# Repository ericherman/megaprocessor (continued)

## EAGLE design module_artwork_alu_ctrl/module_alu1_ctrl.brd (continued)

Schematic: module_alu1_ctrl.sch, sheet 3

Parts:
CMP88, CMP92, CMP94: BUS_SPLIT_DISPLAY

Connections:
BUS_DECODE_ALU_1: CMP92.INPUT
BUS_DECODE_ALU_2: CMP88.INPUT
BUS_DECODE_ALU_3: CMP94.INPUT
K_0: CMP94.P$7 (OUT_6); also elsewhere on the board
K_1: CMP94.P$8 (OUT_7); also elsewhere on the board
K_N: CMP94.P$9 (OUT_8); also elsewhere on the board
OPCODE_IS_ABS: CMP88.P$14 (OUT_13); also elsewhere on the board
OPCODE_IS_ADDQ_GROUP: CMP94.P$6 (OUT_5); also elsewhere on the board
OPCODE_IS_ADDX: CMP88.P$12 (OUT_11); also elsewhere on the board
OPCODE_IS_ADD_GROUP: CMP88.P$9 (OUT_8); also elsewhere on the board
OPCODE_IS_ADD_SP_STATE_2: CMP92.P$15 (OUT_14); also elsewhere on the board
OPCODE_IS_AND_GROUP: CMP88.P$8 (OUT_7); also elsewhere on the board
OPCODE_IS_BIT_XX: CMP88.P$5 (OUT_4); also elsewhere on the board
OPCODE_IS_BIT_XX_N: CMP94.P$2 (OUT_1); also elsewhere on the board
OPCODE_IS_BXX_STATE_2: CMP88.P$1 (OUT_0); also elsewhere on the board
OPCODE_IS_CMP: CMP94.P$1 (OUT_0); also elsewhere on the board
OPCODE_IS_CMP_GROUP: CMP94.P$10 (OUT_9); also elsewhere on the board
OPCODE_IS_DIV: CMP88.P$15 (OUT_14); also elsewhere on the board
OPCODE_IS_DIVS_STATE_0: CMP92.P$2 (OUT_1); also elsewhere on the board
OPCODE_IS_DIV_STATE_0: CMP92.P$7 (OUT_6); also elsewhere on the board
OPCODE_IS_INDIRECT_POSTINC: CMP92.P$9 (OUT_8); also elsewhere on the board
OPCODE_IS_INV: CMP94.P$3 (OUT_2); also elsewhere on the board
OPCODE_IS_JMP_R0: CMP92.P$11 (OUT_10); also elsewhere on the board
OPCODE_IS_JSR_ABS: CMP92.P$14 (OUT_13); also elsewhere on the board
OPCODE_IS_JSR_R0: CMP92.P$5 (OUT_4); also elsewhere on the board
OPCODE_IS_JSR_X_STATE_7: CMP92.P$8 (OUT_7); also elsewhere on the board
OPCODE_IS_LOGIC_GROUP: CMP88.P$3 (OUT_2); also elsewhere on the board
OPCODE_IS_MOVER: CMP94.P$11 (OUT_10); also elsewhere on the board
OPCODE_IS_MOVE_R0_SP_STATE_0: CMP92.P$12 (OUT_11); also elsewhere on the board
OPCODE_IS_MOVE_SP_R0: CMP92.P$10 (OUT_9); also elsewhere on the board
OPCODE_IS_MULS: CMP88.P$13 (OUT_12); also elsewhere on the board
OPCODE_IS_MUL_N: CMP92.P$13 (OUT_12); also elsewhere on the board
OPCODE_IS_NEG: CMP88.P$4 (OUT_3); also elsewhere on the board
OPCODE_IS_NEGX: CMP88.P$10 (OUT_9); also elsewhere on the board
OPCODE_IS_OR: CMP88.P$7 (OUT_6); also elsewhere on the board
OPCODE_IS_OR_GROUP: CMP94.P$12 (OUT_11); also elsewhere on the board
OPCODE_IS_PUSH_PS: CMP92.P$3 (OUT_2); also elsewhere on the board
OPCODE_IS_PUSH_RA: CMP92.P$4 (OUT_3); also elsewhere on the board
OPCODE_IS_SHIFT_XX: CMP88.P$2 (OUT_1); also elsewhere on the board
OPCODE_IS_SQRT: CMP88.P$16 (OUT_15); also elsewhere on the board
OPCODE_IS_STACK_GROUP: CMP94.P$5 (OUT_4); also elsewhere on the board
OPCODE_IS_STACK_REL_STATE_2: CMP92.P$16 (OUT_15); also elsewhere on the board
OPCODE_IS_SUB: CMP88.P$6 (OUT_5); also elsewhere on the board
OPCODE_IS_SUBX: CMP88.P$11 (OUT_10); also elsewhere on the board
OPCODE_IS_SUB_GROUP: CMP94.P$4 (OUT_3); also elsewhere on the board
OPCODE_IS_TRAP: CMP92.P$6 (OUT_5); also elsewhere on the board
OPCODE_IS_XOR_GROUP: CMP94.P$13 (OUT_12); also elsewhere on the board
SHIFT_IS_SHIFTING: CMP92.P$1 (OUT_0); also elsewhere on the board

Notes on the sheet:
clBit shift_is_shifting; // 0 clBit opcode_is_divs_state_0; // 1 clBit opcode_is_push_ps; // 2 clBit opcode_is_push_ra; // 3 clBit opcode_is_jsr_r0; // 4 clBit opcode_is_trap; // 5 clBit opcode_is_div_state_0; // 6 clBit opcode_is_jsr_x_state_7; // 7 clBit opcode_is_indirect_postinc; // 8 clBit opc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
clBit opcode_is_bxx_state_2; // 0 clBit opcode_is_shift_xx; // 1 clBit opcode_is_logic_group; // 2 clBit opcode_is_neg; // 3 clBit opcode_is_bit_xx; // 4 clBit opcode_is_sub; // 5 clBit opcode_is_or; // 6 clBit opcode_is_and_group; // 7 clBit opcode_is_add_group; // 8 clBit opcode_is_negx; // 9 clB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
clBit opcode_is_cmp; // 0 clBit opcode_is_bit_xx_n; // 1 clBit opcode_is_inv; // 2 clBit opcode_is_sub_group; // 3 clBit opcode_is_stack_group; // 4 clBit opcode_is_addq_group; // 5 clBit k_0; // 6 clBit k_1; // 7 clBit k_m; // 8 clBit opcode_is_cmp_group; // 9 clBit opcode_is_mover; // 10 clBit op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

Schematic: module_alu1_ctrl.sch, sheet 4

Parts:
CMP35: DECODER16
CMP39: BUS_CONSTRUCT_DISPLAY; BUS_SPLIT_DISPLAY
CMP40: BUS_2_BUS; BUS2BUS

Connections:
H_1: CMP35.A1; also elsewhere on the board
H_2: CMP35.A2; also elsewhere on the board
H_3: CMP35.A3; also elsewhere on the board
unnamed: CMP35.P0, CMP39.P$15 (IN_14)
unnamed: CMP35.P1, CMP39.P$14 (IN_13)
unnamed: CMP35.P2, CMP39.P$13 (IN_12)
unnamed: CMP35.P3, CMP39.P$12 (IN_11)
unnamed: CMP35.P4, CMP39.P$11 (IN_10)
unnamed: CMP35.P5, CMP39.P$10 (IN_9)
unnamed: CMP35.P6, CMP39.P$9 (IN_8)
unnamed: CMP35.P7, CMP39.P$8 (IN_7)
unnamed: CMP35.P8, CMP39.P$7 (IN_6)
unnamed: CMP35.P9, CMP39.P$6 (IN_5)
unnamed: CMP35.P10, CMP39.P$5 (IN_4)
unnamed: CMP35.P11, CMP39.P$4 (IN_3)
unnamed: CMP35.P12, CMP39.P$3 (IN_2)
unnamed: CMP35.P13, CMP39.P$2 (IN_1)
unnamed: CMP35.P14, CMP39.P$1 (IN_0)
unnamed: CMP35.P15, CMP39.P$16 (IN_15)
unnamed: CMP39.INPUT (OUT), CMP40.P$1 (IN)

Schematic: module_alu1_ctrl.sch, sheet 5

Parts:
CMP10: DECODER4
CMP20: 2AND
CMP24, CMP27: 2OR
CMP26: 8OR
CMP41: 1BUF

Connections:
ALU1_X_MUX_RA__SET_A: CMP26.OUT_P; also elsewhere on the board
ALU1_X_MUX_SHIFT_R3: CMP27.OUT_P; also elsewhere on the board
ALU1_X_MUX_SHIFT_R3_N: CMP27.OUT_M (N); also elsewhere on the board
BIT_SELECT_ENABLE: CMP41.N; also elsewhere on the board
BIT_SHIFT_MODE_CHANGE__ARITH: CMP10.P1; also elsewhere on the board
BIT_SHIFT_MODE_CLEAR__ROTATE: CMP10.P2; also elsewhere on the board
BIT_SHIFT_MODE_CLEAR__ROTATE_N: CMP10.N2; also elsewhere on the board
BIT_SHIFT_MODE_SET__X_ROT: CMP10.P3; also elsewhere on the board
BIT_SHIFT_MODE_TEST__LOGICAL: CMP10.P0
BIT_XX_ACTION_CYCLE: CMP24.OUT_M (N), CMP26.3 (2); also elsewhere on the board
BIT_XX_LOAD_CYCLE: CMP20.OUT_P; also elsewhere on the board
H_6: CMP10.A0; also elsewhere on the board
H_7: CMP10.A1; also elsewhere on the board
OPCODE_IS_ADDQ_GROUP: CMP26.6 (5); also elsewhere on the board
OPCODE_IS_ADD_GROUP: CMP26.2 (1); also elsewhere on the board
OPCODE_IS_AND_GROUP: CMP26.1 (0); also elsewhere on the board
OPCODE_IS_BIT_XX: CMP20.P$1 (1); also elsewhere on the board
OPCODE_IS_BIT_XX_N: CMP24.P$2 (A1); also elsewhere on the board
OPCODE_IS_CMP: CMP26.5 (4); also elsewhere on the board
OPCODE_IS_INV: CMP41.IN; also elsewhere on the board
OPCODE_IS_OR_GROUP: CMP26.8 (7); also elsewhere on the board
OPCODE_IS_SUB: CMP26.7 (6); also elsewhere on the board
OPCODE_IS_XOR_GROUP: CMP26.4 (3); also elsewhere on the board
STATE_1: CMP20.P$2 (2), CMP24.P$1 (A2); also elsewhere on the board
STATE_11: CMP27.P$1 (A2); also elsewhere on the board
STATE_13: CMP27.P$2 (A1); also elsewhere on the board

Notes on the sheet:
bit_select_enable = ~bus_decode_alu_1.opcode_is_inv;
bit_xx_load_cycle = Cpnt_2AND(bus_decode_alu_2.opcode_is_bit_xx, bus_state[1]);
bit_xx_action_cycle = ~Cpnt_2OR(bus_decode_alu_3.opcode_is_bit_xx_n, bus_state[1]);
alu1_x_mux_RA__set_A = Cpnt_8OR(bus_decode_alu_1.opcode_is_add_group, bus_decode_alu_1.opcode_is_addq_group, bus_decode_alu_1.opcode_is_sub, bus_decode_alu_1.opcode_is_cmp, bus_decode_alu_1.opcode_is_and_group, bus_decode_alu_1.opcode_is_or_group, bus_decode_alu_1.opcode_is_xor_group, bit_xx_action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
alu1_x_mux_shift_r3 = Cpnt_2OR(bus_state[13], bus_state[11]);

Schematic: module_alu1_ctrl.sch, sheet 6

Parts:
CMP28, CMP33: 2X2AND_OR
CMP29: 8OR
CMP30: 3OR
CMP31: 4OR
CMP32: 2AND

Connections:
ADDER_X_SPECIAL: CMP28.P$2 (A1); also elsewhere on the board
ADDER_Y_SPECIAL: CMP29.2 (1); also elsewhere on the board
ALU1_X_MUX_RA: CMP28.OUT_P; also elsewhere on the board
ALU1_X_MUX_RA__SET_A: CMP28.P$4 (B1); also elsewhere on the board
ALU1_X_MUX_SHIFT_R3_N: CMP28.P$1 (A0), CMP28.P$3 (B0); also elsewhere on the board
ALU1_Y_MUX_BIT: CMP32.OUT_P; also elsewhere on the board
ALU1_Y_MUX_K: CMP31.OUT_P; also elsewhere on the board
ALU1_Y_MUX_NOT_BIT: CMP33.OUT_P; also elsewhere on the board
ALU1_Y_MUX_RB: CMP30.OUT_P; also elsewhere on the board
ALU1_Y_MUX_RB_A: CMP29.OUT_P, CMP30.P$3 (2)
BIT_SHIFT_MODE_CLEAR__ROTATE: CMP33.P$3 (B0); also elsewhere on the board
BIT_SHIFT_MODE_CLEAR__ROTATE_N: CMP32.P$1 (1); also elsewhere on the board
BIT_XX_ACTION_CYCLE: CMP32.P$2 (2), CMP33.P$4 (B1); also elsewhere on the board
BIT_XX_LOAD_CYCLE: CMP30.P$1 (0); also elsewhere on the board
FLAG_F3: CMP31.1 (0); also elsewhere on the board
OPCODE_IS_ADDQ_GROUP: CMP31.2 (1); also elsewhere on the board
OPCODE_IS_ADD_GROUP: CMP29.4 (3); also elsewhere on the board
OPCODE_IS_AND_GROUP: CMP29.8 (7); also elsewhere on the board
OPCODE_IS_CMP_GROUP: CMP29.3 (2); also elsewhere on the board
OPCODE_IS_INV: CMP33.P$1 (A0), CMP33.P$2 (A1); also elsewhere on the board
OPCODE_IS_MOVER: CMP29.5 (4); also elsewhere on the board
OPCODE_IS_OR: CMP29.7 (6); also elsewhere on the board
OPCODE_IS_SHIFT_XX: CMP30.P$2 (1); also elsewhere on the board
OPCODE_IS_STACK_GROUP: CMP31.3 (2); also elsewhere on the board
OPCODE_IS_SUB_GROUP: CMP29.1 (0); also elsewhere on the board
OPCODE_IS_XOR_GROUP: CMP29.6 (5); also elsewhere on the board
STATE_13: CMP31.4 (3); also elsewhere on the board

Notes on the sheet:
alu1_x_mux_RA = Cpnt_2x2AND_OR(alu1_x_mux_RA__set_A, ~alu1_x_mux_shift_r3, bus_rnx_specials.adder_x_special,~alu1_x_mux_shift_r3);
alu1_y_mux_RB_A = Cpnt_8OR(bus_decode_alu_1.opcode_is_and_group, bus_decode_alu_1.opcode_is_or, bus_decode_alu_1.opcode_is_xor_group, bus_decode_alu_1.opcode_is_mover, bus_decode_alu_1.opcode_is_add_group, bus_decode_alu_1.opcode_is_sub_group, bus_decode_alu_1.opcode_is_cmp_group, bus_rnx_specials.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
alu1_y_mux_RB = Cpnt_3OR(alu1_y_mux_RB_A, bus_decode_alu_2.opcode_is_shift_xx, bit_xx_load_cycle);
alu1_y_mux_k = Cpnt_4OR(bus_decode_alu_1.opcode_is_addq_group, bus_decode_alu_1.opcode_is_stack_group, bus_state[13], bus_PS[WiC_PS_FLAG_INDEX_F3]);
alu1_y_mux_bit = Cpnt_2AND(bit_xx_action_cycle, ~bit_shift_mode_decode.Output()[BIT_SHIFT_MODE_CLEAR]);
alu1_y_mux_not_bit = Cpnt_2x2AND_OR(bit_xx_action_cycle, bit_shift_mode_decode.Output()[BIT_SHIFT_MODE_CLEAR], bus_decode_alu_1.opcode_is_inv, bus_decode_alu_1.opcode_is_inv);

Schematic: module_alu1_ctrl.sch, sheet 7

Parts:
CMP3: 2AND
CMP4: 2X2AND_OR
CMP5: 8OR
CMP6: 2OR
CMP7: 4X2AND_OR
CMP57: 1BUF

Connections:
ADD1_CARRY_INPUT_BIT: CMP7.OUT_P; also elsewhere on the board
ADD1_DO_SUBTRACT: CMP5.OUT_P, CMP7.P$3 (B0); also elsewhere on the board
DO_SUBTRACT__SET_A: CMP4.OUT_P, CMP5.7 (6)
FLAG_X: CMP7.P$7 (D0), CMP57.IN; also elsewhere on the board
FLAG_X_N: CMP7.P$5 (C0), CMP57.N
H_4: CMP3.P$1 (1); also elsewhere on the board
unnamed: CMP7.P$1 (A0), CMP7.P$2 (A1)
NEGATE_FOR_SHIFT: CMP3.OUT_P, CMP5.2 (1)
OPCODE_IS_ABS: CMP4.P$4 (B1); also elsewhere on the board
OPCODE_IS_ADDX: CMP7.P$8 (D1); also elsewhere on the board
OPCODE_IS_CMP: CMP5.3 (2); also elsewhere on the board
OPCODE_IS_DIV: CMP5.8 (7); also elsewhere on the board
OPCODE_IS_MULS: CMP4.P$2 (A1); also elsewhere on the board
OPCODE_IS_NEGX: CMP5.5 (4), CMP6.P$1 (A2); also elsewhere on the board
OPCODE_IS_SHIFT_XX: CMP3.P$2 (2); also elsewhere on the board
OPCODE_IS_SQRT: CMP5.1 (0); also elsewhere on the board
OPCODE_IS_SUBX: CMP5.4 (3), CMP6.P$2 (A1); also elsewhere on the board
OPCODE_IS_SUBX_NEGX: CMP6.OUT_P, CMP7.P$6 (C1)
OPCODE_IS_SUBX_NEGX_N: CMP6.OUT_M (N), CMP7.P$4 (B1)
OPCODE_IS_SUB_GROUP: CMP5.6 (5); also elsewhere on the board
RA_MUX_IS_N: CMP4.P$3 (B0); also elsewhere on the board
STATE_3: CMP4.P$1 (A0); also elsewhere on the board

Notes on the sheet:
negate_for_shift = Cpnt_2AND(bus_decode_alu_2.opcode_is_shift_xx, bus_H[4]);
add1_do_subtract__set_A = Cpnt_2x2AND_OR(bus_decode_alu_2.opcode_is_abs, bus_ra_flags.RA_mux_is_n, bus_decode_alu_2.opcode_is_muls, bus_state[3]);
add1_do_subtract = Cpnt_8OR(bus_decode_alu_1.opcode_is_sub_group, bus_decode_alu_1.opcode_is_cmp, bus_decode_alu_2.opcode_is_subx, bus_decode_alu_2.opcode_is_negx, add1_do_subtract__set_A, bus_decode_alu_2.opcode_is_sqrt, bus_decode_alu_2.opcode_is_div, negate_for_shift); // MOPUP
opcode_is_subx_negx = Cpnt_2OR(bus_decode_alu_2.opcode_is_subx, bus_decode_alu_2.opcode_is_negx);
add1_input_carry_bit = Cpnt_4x2AND_OR(bus_decode_alu_2.opcode_is_addx, bus_PS[WiC_PS_FLAG_INDEX_X], // ADDX opcode_is_subx_negx, ~bus_PS[WiC_PS_FLAG_INDEX_X], // SUBX ~opcode_is_subx_negx, add1_do_subtract, // SUB BIT_VAL_0,BIT_VAL_0); // MOPUP

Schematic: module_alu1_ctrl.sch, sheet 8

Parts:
CMP2, CMP8: 3OR
CMP9: 2OR
CMP25, CMP38: 1BUF
CMP36, CMP37: 3AND

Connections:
H_4: CMP38.IN; also elsewhere on the board
IS_SHIFTING_LEFT: CMP36.OUT_P; also elsewhere on the board
IS_SHIFTING_RIGHT: CMP37.OUT_P; also elsewhere on the board
OPCODE_IS_ADDQ_GROUP: CMP2.P$2 (1); also elsewhere on the board
OPCODE_IS_ADDX: CMP2.P$3 (2); also elsewhere on the board
OPCODE_IS_ADD_GROUP: CMP2.P$1 (0); also elsewhere on the board
OPCODE_IS_CMP: CMP8.P$3 (2); also elsewhere on the board
OPCODE_IS_NEG: CMP9.P$1 (A2); also elsewhere on the board
OPCODE_IS_NEGX: CMP9.P$2 (A1); also elsewhere on the board
OPCODE_IS_SHIFT_XX: CMP36.P$3 (3), CMP37.P$3 (3); also elsewhere on the board
OPCODE_IS_SUB: CMP8.P$1 (0); also elsewhere on the board
OPCODE_IS_SUBX: CMP8.P$2 (1); also elsewhere on the board
SHIFT_LEFT: CMP36.P$1 (1), CMP38.N
SHIFT_RIGHT: CMP37.P$2 (2), CMP38.P
STATE_1: CMP25.IN; also elsewhere on the board
STATE_1_N: CMP25.N, CMP36.P$2 (2), CMP37.P$1 (1); also elsewhere on the board
USE_ADD_V: CMP2.OUT_P; also elsewhere on the board
USE_NEG_V: CMP9.OUT_P; also elsewhere on the board
USE_SUB_V: CMP8.OUT_P; also elsewhere on the board

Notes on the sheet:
use_add_V = Cpnt_3OR(bus_decode_alu_1.opcode_is_add_group, bus_decode_alu_1.opcode_is_addq_group, bus_decode_alu_2.opcode_is_addx);
use_sub_V = Cpnt_3OR(bus_decode_alu_1.opcode_is_sub, bus_decode_alu_1.opcode_is_cmp, bus_decode_alu_2.opcode_is_subx);
use_neg_V = Cpnt_2OR(bus_decode_alu_2.opcode_is_neg,bus_decode_alu_2.opcode_is_negx);
is_shifting_right = Cpnt_3AND(bus_decode_alu_2.opcode_is_shift_xx, bus_H[4], ~bus_state[1]);
is_shifting_left = Cpnt_3AND(bus_decode_alu_2.opcode_is_shift_xx, ~bus_H[4], ~bus_state[1]);

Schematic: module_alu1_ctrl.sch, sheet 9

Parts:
CMP11, CMP16, CMP19, CMP23: 2AND
CMP18: 2OR
CMP34: 3OR

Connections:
ARITH_RIGHT_INPUT: CMP19.OUT_P, CMP34.P$1 (0)
BIT_SHIFT_MODE_CHANGE__ARITH: CMP19.P$1 (1); also elsewhere on the board
BIT_SHIFT_MODE_CLEAR__ROTATE: CMP16.P$1 (1), CMP23.P$1 (1); also elsewhere on the board
BIT_SHIFT_MODE_SET__X_ROT: CMP11.P$1 (1); also elsewhere on the board
FLAG_X: CMP11.P$2 (2); also elsewhere on the board
LEFT_SHIFT_INPUT: CMP18.OUT_P; also elsewhere on the board
RA_MUX_IS_N: CMP16.P$2 (2), CMP19.P$2 (2); also elsewhere on the board
RA_MUX_LSB: CMP23.P$2 (2); also elsewhere on the board
RIGHT_SHIFT_INPUT: CMP34.OUT_P; also elsewhere on the board
ROT_LEFT_INPUT: CMP16.OUT_P, CMP18.P$2 (A1)
ROT_RIGHT_INPUT: CMP23.OUT_P, CMP34.P$3 (2)
X_ROT_INPUT: CMP11.OUT_P, CMP18.P$1 (A2), CMP34.P$2 (1)

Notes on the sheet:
x_rot_input = Cpnt_2AND(bit_shift_mode_decode.Output()[BIT_SHIFT_MODE_X_ROT], bus_PS[WiC_PS_FLAG_INDEX_X]);
rot_left_input = Cpnt_2AND(bit_shift_mode_decode.Output()[BIT_SHIFT_MODE_ROTATE], bus_ra_flags.RA_mux_is_n);
left_shift_input = Cpnt_2OR(rot_left_input, x_rot_input);
arith_right_input = Cpnt_2AND(bit_shift_mode_decode.Output()[BIT_SHIFT_MODE_ARITH], bus_ra_flags.RA_mux_is_n);
rot_right_input = Cpnt_2AND(bit_shift_mode_decode.Output()[BIT_SHIFT_MODE_ROTATE], bus_ra_flags.RA_mux_lsb);
right_shift_input = Cpnt_3OR(arith_right_input, rot_right_input, x_rot_input);

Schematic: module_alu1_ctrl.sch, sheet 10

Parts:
CMP42, CMP43, CMP45: 2X2AND_OR
CMP44: 2OR
CMP46: 3OR

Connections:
ALU1_OUTPUT_MUX_ADDER: CMP46.OUT_M (N); also elsewhere on the board
ALU1_OUTPUT_MUX_LOGIC: CMP45.OUT_P, CMP46.P$3 (2); also elsewhere on the board
AND: CMP42.OUT_P, CMP44.P$2 (A1); also elsewhere on the board
BIT_SHIFT_MODE_CLEAR__ROTATE: CMP42.P$3 (B0); also elsewhere on the board
BIT_SHIFT_MODE_SET__X_ROT: CMP43.P$3 (B0); also elsewhere on the board
IS_SHIFTING_LEFT: CMP46.P$2 (1); also elsewhere on the board
IS_SHIFTING_RIGHT: CMP46.P$1 (0); also elsewhere on the board
OPCODE_IS_AND_GROUP: CMP42.P$1 (A0), CMP42.P$2 (A1); also elsewhere on the board
OPCODE_IS_BIT_XX: CMP42.P$4 (B1), CMP43.P$4 (B1), CMP45.P$4 (B1); also elsewhere on the board
OPCODE_IS_LOGIC_GROUP: CMP45.P$1 (A0), CMP45.P$2 (A1); also elsewhere on the board
OPCODE_IS_OR: CMP43.P$1 (A0), CMP43.P$2 (A1); also elsewhere on the board
OR: CMP43.OUT_P, CMP44.P$1 (A2); also elsewhere on the board
STATE_1_N: CMP45.P$3 (B0); also elsewhere on the board
XOR: CMP44.OUT_M (N); also elsewhere on the board

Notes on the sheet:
logic_output_mux_and = Cpnt_2x2AND_OR(bus_decode_alu_2.opcode_is_bit_xx, bit_shift_mode_decode.Output()[BIT_SHIFT_MODE_CLEAR], bus_decode_alu_1.opcode_is_and_group, bus_decode_alu_1.opcode_is_and_group);
logic_output_mux_or = Cpnt_2x2AND_OR(bus_decode_alu_2.opcode_is_bit_xx, bit_shift_mode_decode.Output()[BIT_SHIFT_MODE_SET], bus_decode_alu_1.opcode_is_or, bus_decode_alu_1.opcode_is_or);
logic_output_mux_xor = ~Cpnt_2OR(logic_output_mux_and, logic_output_mux_or);
alu_output_mux_logic = Cpnt_2x2AND_OR(bus_decode_alu_2.opcode_is_bit_xx, ~bus_state[1], bus_decode_alu_1.opcode_is_logic_group, bus_decode_alu_1.opcode_is_logic_group);
alu_output_mux_adder = ~Cpnt_3OR(alu_output_mux_logic, is_shifting_left, is_shifting_right);

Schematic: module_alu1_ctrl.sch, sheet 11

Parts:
CMP14, CMP48: 2X2AND_OR
CMP53: 4OR
CMP56: 3AND
CMP60, CMP62: 5OR

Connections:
ADD2_MUX_WEIGHT: CMP53.1 (0), CMP56.OUT_P; also elsewhere on the board
ADD2_X_MUX_PC: CMP62.OUT_M (N); also elsewhere on the board
ADD2_X_MUX_RI: CMP60.OUT_P, CMP62.4 (3); also elsewhere on the board
ADD2_X_MUX_RI__H: CMP60.4 (3); also elsewhere on the board
ADD2_X_MUX_RI__SET_A: CMP14.OUT_P, CMP60.1 (0)
ADD2_X_MUX_RI__SP: CMP60.5 (4); also elsewhere on the board
ADD2_X_ZERO: CMP53.OUT_P, CMP62.3 (2)
FLAG_F6: CMP56.P$1 (1); also elsewhere on the board
JMP_R0_MOVE_SP_R0_STATE_0: CMP48.OUT_P, CMP53.4 (3); also elsewhere on the board
OPCODE_IS_DIV_STATE_0: CMP53.2 (1); also elsewhere on the board
OPCODE_IS_INDIRECT_POSTINC: CMP14.P$3 (B0); also elsewhere on the board
OPCODE_IS_JMP_R0: CMP48.P$3 (B0); also elsewhere on the board
OPCODE_IS_JSR_X_STATE_7: CMP53.3 (2); also elsewhere on the board
OPCODE_IS_MOVE_SP_R0: CMP48.P$1 (A0); also elsewhere on the board
OPCODE_IS_SHIFT_XX: CMP56.P$2 (2); also elsewhere on the board
R0_IS_N: CMP14.P$1 (A0); also elsewhere on the board
STATE_0: CMP14.P$4 (B1), CMP48.P$2 (A1), CMP48.P$4 (B1); also elsewhere on the board
STATE_2: CMP56.P$3 (3); also elsewhere on the board
STATE_10: CMP62.1 (0); also elsewhere on the board
STATE_11: CMP60.3 (2); also elsewhere on the board
STATE_12: CMP60.2 (1); also elsewhere on the board
STATE_13: CMP62.5 (4); also elsewhere on the board
STATE_14: CMP14.P$2 (A1), CMP62.2 (1); also elsewhere on the board

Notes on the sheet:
opcode_is_jmp_r0_move_sp_r0_state_0 = Cpnt_2x2AND_OR(bus_state[0],bus_decode_alu_3.opcode_is_jmp_r0, bus_state[0],bus_decode_alu_2.opcode_is_move_sp_r0);
add2_mux_weight = Cpnt_3AND(bus_state[2], bus_decode_alu_2.opcode_is_shift_xx, bus_PS[WiC_PS_FLAG_INDEX_F6]);
add2_x_mux_ri__set_A = Cpnt_2x2AND_OR(bus_state[0], bus_decode_alu_1.opcode_is_indirect_postinc, bus_state[14], bus_rn_arith_flags.r0_is_n);
add2_x_mux_ri = Cpnt_5OR(add2_x_mux_ri__set_A, bus_rnx_specials.add2_x_mux_ri__h, bus_rnx_specials.add2_x_mux_ri__sp, bus_state[11], bus_state[12]);
add2_x_sqrt_mask = bus_state[10]; add2_x_shift_r2 = bus_state[13];
add2_x_zero = Cpnt_4OR(opcode_is_jmp_r0_move_sp_r0_state_0, bus_decode_alu_3.opcode_is_jsr_x_state_7 , bus_decode_alu_3.opcode_is_div_state_0, add2_mux_weight);
add2_x_mux_pc = ~Cpnt_5OR(add2_x_shift_r2 , add2_x_mux_ri, add2_x_zero, add2_x_sqrt_mask, bus_state[14]);

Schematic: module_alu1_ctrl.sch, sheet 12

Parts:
CMP17: 3OR
CMP47: 2AND
CMP49, CMP50: 4OR
CMP51: 2OR
CMP52: 4X2AND_OR

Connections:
ADD2_Y_MUX_0: CMP51.OUT_P; also elsewhere on the board
ADD2_Y_MUX_0__MUL: CMP17.OUT_M (N), CMP51.P$2 (A1)
ADD2_Y_MUX_H: CMP49.OUT_P; also elsewhere on the board
ADD2_Y_MUX_H__JSR: CMP47.OUT_P, CMP49.1 (0)
ADD2_Y_MUX_R0: CMP50.OUT_P; also elsewhere on the board
ADD2_Y_MUX_R0__SET_A: CMP50.4 (3), CMP52.OUT_P
JMP_R0_MOVE_SP_R0_STATE_0: CMP50.3 (2); also elsewhere on the board
unnamed: CMP52.P$1 (A0), CMP52.P$2 (A1)
OPCODE_IS_ADD_SP_STATE_2: CMP49.2 (1); also elsewhere on the board
OPCODE_IS_BXX_STATE_2: CMP49.4 (3); also elsewhere on the board
OPCODE_IS_DIV_STATE_0: CMP50.1 (0); also elsewhere on the board
OPCODE_IS_JSR_ABS: CMP47.P$2 (2); also elsewhere on the board
OPCODE_IS_JSR_R0: CMP52.P$6 (C1); also elsewhere on the board
OPCODE_IS_MOVE_R0_SP_STATE_0: CMP51.P$1 (A2); also elsewhere on the board
OPCODE_IS_MUL_N: CMP17.P$2 (1); also elsewhere on the board
OPCODE_IS_STACK_REL_STATE_2: CMP49.3 (2); also elsewhere on the board
R1_IS_N: CMP17.P$1 (0), CMP52.P$3 (B0), CMP52.P$7 (D0); also elsewhere on the board
STATE_3: CMP17.P$3 (2); also elsewhere on the board
STATE_7: CMP47.P$1 (1), CMP52.P$5 (C0); also elsewhere on the board
STATE_10: CMP50.2 (1); also elsewhere on the board
STATE_13: CMP52.P$8 (D1); also elsewhere on the board
STATE_14: CMP52.P$4 (B1); also elsewhere on the board

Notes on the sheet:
add2_y_mux_h__jsr = Cpnt_2AND(bus_state[7], bus_decode_alu_2.opcode_is_jsr_abs);
add2_y_mux_h = Cpnt_4OR(bus_decode_alu_3.opcode_is_bxx_state_2, bus_decode_alu_3.opcode_is_stack_rel_state_2, bus_decode_alu_3.opcode_is_add_sp_state_2, add2_y_mux_h__jsr);
add2_y_mux_0__mul = ~Cpnt_3OR(bus_decode_alu_1.opcode_is_mul_n, bus_rn_arith_flags.r1_is_n, bus_state[3]);
add2_y_mux_0 = Cpnt_2OR(add2_y_mux_0__mul, bus_decode_alu_3.opcode_is_move_r0_sp_state_0);
add2_y_mux_r0__set_A = Cpnt_4x2AND_OR(bus_state[13], bus_rn_arith_flags.r1_is_n, bus_decode_alu_2.opcode_is_jsr_r0, bus_state[7], bus_state[14], bus_rn_arith_flags.r1_is_n, BIT_VAL_0, BIT_VAL_0); // MOPUP
add2_y_mux_r0 = Cpnt_4OR(add2_y_mux_r0__set_A, opcode_is_jmp_r0_move_sp_r0_state_0, bus_state[10], bus_decode_alu_3.opcode_is_div_state_0);

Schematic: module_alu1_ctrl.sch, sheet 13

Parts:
CMP54: 5OR
CMP55: 8X2AND_OR
CMP59: 3AND
CMP61: 2OR

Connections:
ADD2_CARRY_IN: CMP61.OUT_P; also elsewhere on the board
ADD2_DO_SUBTRACT: CMP55.OUT_P, CMP61.P$2 (A1); also elsewhere on the board
ADD2_MUX_WEIGHT: CMP54.3 (2), CMP59.P$3 (3); also elsewhere on the board
ADD2_WEIGHT_BIT: CMP59.OUT_P, CMP61.P$1 (A2)
ADD2_Y_MUX_0: CMP54.4 (3); also elsewhere on the board
ADD2_Y_MUX_H: CMP54.5 (4); also elsewhere on the board
ADD2_Y_MUX_P1: CMP54.OUT_M (N); also elsewhere on the board
ADD2_Y_MUX_R0: CMP54.2 (1); also elsewhere on the board
unnamed: CMP55.P$1 (A0), CMP55.P$2 (A1)
OPCODE_IS_DIVS_STATE_0: CMP55.P$6 (C1); also elsewhere on the board
OPCODE_IS_JSR_R0: CMP55.P$12 (F2); also elsewhere on the board
OPCODE_IS_PUSH_PS: CMP55.P$8 (D1); also elsewhere on the board
OPCODE_IS_PUSH_RA: CMP55.P$10 (E2); also elsewhere on the board
OPCODE_IS_STACK_GROUP: CMP55.P$16 (H2); also elsewhere on the board
OPCODE_IS_TRAP: CMP55.P$13 (G1); also elsewhere on the board
R0_IS_N: CMP55.P$5 (C0); also elsewhere on the board
RA_MUX_LSB: CMP59.P$2 (2); also elsewhere on the board
SHIFT_IS_SHIFTING: CMP59.P$1 (1); also elsewhere on the board
STATE_0: CMP55.P$7 (D0), CMP55.P$9 (E1), CMP55.P$11 (F1); also elsewhere on the board
STATE_6: CMP55.P$15 (H1); also elsewhere on the board
STATE_7: CMP55.P$14 (G2); also elsewhere on the board
STATE_14: CMP54.1 (0); also elsewhere on the board
STATE_15: CMP55.P$3 (B0), CMP55.P$4 (B1); also elsewhere on the board

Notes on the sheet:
add2_y_mux_p1 = ~Cpnt_5OR(add2_y_mux_h, add2_y_mux_0, add2_y_mux_r0, bus_state[14],add2_mux_weight);
add2_do_subtract = Cpnt_8x2AND_OR(bus_decode_alu_1.opcode_is_stack_group, bus_state[6] , bus_decode_alu_2.opcode_is_trap, bus_state[7], bus_decode_alu_2.opcode_is_jsr_r0, bus_state[0], bus_decode_alu_2.opcode_is_push_ra, bus_state[0], bus_decode_alu_2.opcode_is_push_ps, bus_state[0], bus_decode_alu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
add2_weight_bit = Cpnt_3AND(add2_mux_weight, bus_ra_flags.RA_mux_lsb, bus_decode_alu_3.shift_is_shifting);
add2_carry_in = Cpnt_2OR(add2_do_subtract,add2_weight_bit);

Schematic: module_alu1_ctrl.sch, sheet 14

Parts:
CMP65, CMP66, CMP67: BUS_CONSTRUCT_DISPLAY; BUS_SPLIT_DISPLAY

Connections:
ADD1_CARRY_INPUT_BIT: CMP65.P$2 (IN_1); also elsewhere on the board
ADD1_DO_SUBTRACT: CMP65.P$1 (IN_0); also elsewhere on the board
ADD2_CARRY_IN: CMP67.P$10 (IN_9); also elsewhere on the board
ADD2_DO_SUBTRACT: CMP67.P$9 (IN_8); also elsewhere on the board
ADD2_MUX_WEIGHT: CMP67.P$1 (IN_0); also elsewhere on the board
ADD2_X_MUX_PC: CMP67.P$7 (IN_6); also elsewhere on the board
ADD2_X_MUX_RI: CMP67.P$5 (IN_4); also elsewhere on the board
ADD2_Y_MUX_H: CMP67.P$2 (IN_1); also elsewhere on the board
ADD2_Y_MUX_P1: CMP67.P$4 (IN_3); also elsewhere on the board
ADD2_Y_MUX_R0: CMP67.P$3 (IN_2); also elsewhere on the board
ALU1_OUTPUT_MUX_ADDER: CMP65.P$11 (IN_10); also elsewhere on the board
ALU1_OUTPUT_MUX_LOGIC: CMP65.P$10 (IN_9); also elsewhere on the board
ALU1_X_MUX_RA: CMP66.P$6 (IN_5); also elsewhere on the board
ALU1_X_MUX_SHIFT_R3: CMP66.P$7 (IN_6); also elsewhere on the board
ALU1_Y_MUX_BIT: CMP66.P$11 (IN_10); also elsewhere on the board
ALU1_Y_MUX_K: CMP66.P$8 (IN_7); also elsewhere on the board
ALU1_Y_MUX_NOT_BIT: CMP66.P$10 (IN_9); also elsewhere on the board
ALU1_Y_MUX_RB: CMP66.P$9 (IN_8); also elsewhere on the board
AND: CMP65.P$6 (IN_5); also elsewhere on the board
BIT_SELECT_ENABLE: CMP66.P$1 (IN_0); also elsewhere on the board
BUS_ADD2_CONTROL: CMP67.INPUT (OUT)
BUS_ALU1_INPUT_CTRL: CMP66.INPUT (OUT)
BUS_ALU1_OPERATION_CTRL: CMP65.INPUT (OUT)
H_0: CMP66.P$2 (IN_1); also elsewhere on the board
H_1: CMP66.P$3 (IN_2); also elsewhere on the board
H_2: CMP66.P$4 (IN_3); also elsewhere on the board
H_3: CMP66.P$5 (IN_4); also elsewhere on the board
H_4: CMP65.P$3 (IN_2); also elsewhere on the board
IS_SHIFTING_LEFT: CMP65.P$13 (IN_12); also elsewhere on the board
IS_SHIFTING_RIGHT: CMP65.P$12 (IN_11); also elsewhere on the board
K_0: CMP66.P$14 (IN_13); also elsewhere on the board
K_1: CMP66.P$13 (IN_12); also elsewhere on the board
K_N: CMP66.P$12 (IN_11); also elsewhere on the board
LEFT_SHIFT_INPUT: CMP65.P$14 (IN_13); also elsewhere on the board
unnamed: CMP66.P$15 (IN_14), CMP66.P$16 (IN_15)
unnamed: CMP67.P$11 (IN_10), CMP67.P$12 (IN_11), CMP67.P$13 (IN_12), CMP67.P$14 (IN_13), CMP67.P$15 (IN_14), CMP67.P$16 (IN_15)
OR: CMP65.P$5 (IN_4); also elsewhere on the board
RIGHT_SHIFT_INPUT: CMP65.P$15 (IN_14); also elsewhere on the board
STATE_10: CMP67.P$8 (IN_7); also elsewhere on the board
STATE_13: CMP67.P$6 (IN_5); also elsewhere on the board
USE_ADD_V: CMP65.P$7 (IN_6); also elsewhere on the board
USE_NEG_V: CMP65.P$9 (IN_8); also elsewhere on the board
USE_SUB_V: CMP65.P$8 (IN_7); also elsewhere on the board
XOR: CMP65.P$4 (IN_3); also elsewhere on the board

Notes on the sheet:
clBit bit_select_enable; // 0 clBitField bit_code; // 1-4 clBit alu1_x_mux_RA; // 5 clBit alu1_x_mux_shift_r3; // 6 clBit alu1_y_mux_k; // 7 clBit alu1_y_mux_RB; // 8 clBit alu1_y_mux_not_bit; // 9 clBit alu1_y_mux_bit; // 10 clBit k_m; // 11 clBit k_1; // 12 clBit k_0; // 13
clBit do_subtract; // 0 clBit input_carry_bit; // 1 clBit H_4; // 2 clBit xor; // 3 clBit or; // 4 clBit and; // 5 clBit use_add_V; // 6 clBit use_sub_V; // 7 clBit use_neg_V; // 8 clBit alu_output_mux_logic; // 9 clBit alu_output_mux_adder; // 10 clBit is_shifting_right; // 11 clBit is_shifting_le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
clBit add2_y_mux_weight; // 0 clBit add2_y_mux_h; // 1 clBit add2_y_mux_r0; // 2 clBit add2_y_mux_p1; // 3 clBit add2_x_mux_ri; // 4 clBit add2_x_mux_shift_r2; // 5 clBit add2_x_mux_pc; // 6 clBit add2_x_mux_sqrt_mask; // 7 clBit add2_do_subtract; // 8 clBit add2_carry_in; // 9

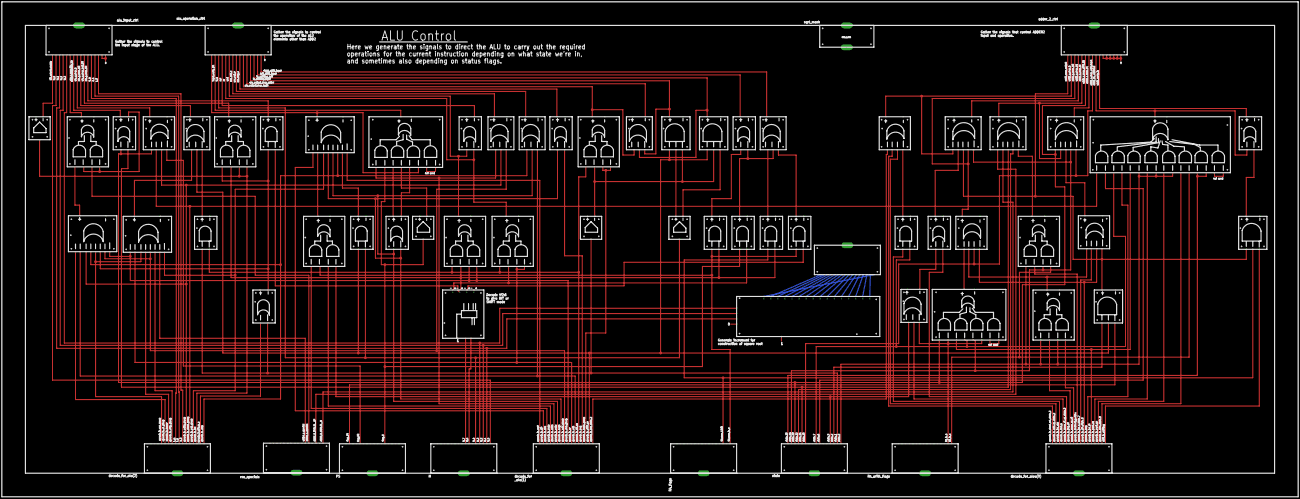
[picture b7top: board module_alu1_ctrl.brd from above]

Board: 2 copper layers, 1397.0 x 533.4 mm, 67 parts (0 on the bottom side), 155 nets.

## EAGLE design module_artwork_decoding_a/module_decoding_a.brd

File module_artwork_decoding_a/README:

Decode A

This bundles together signals from the Opcode Decode module for routing
to other modules. In particular the State and Special Purpose Control
modules. As well as routing it also generates some signals required by
both those modules to begin the task of working out what needs to be
done this cycle.

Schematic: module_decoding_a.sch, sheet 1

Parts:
CMP13, CMP15, CMP17, CMP90: BUS_SPLIT_DISPLAY

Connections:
BUS_INSTR: CMP15.INPUT
BUS_PS: CMP17.INPUT
BUS_STATE: CMP13.INPUT
FLAG_C: CMP17.P$6 (OUT_5)
FLAG_D: CMP17.P$7 (OUT_6)
FLAG_F0: CMP17.P$9 (OUT_8)
FLAG_F1: CMP17.P$10 (OUT_9)
FLAG_F2: CMP17.P$11 (OUT_10); also elsewhere on the board
FLAG_F3: CMP17.P$12 (OUT_11)
FLAG_F4: CMP17.P$13 (OUT_12); also elsewhere on the board
FLAG_F5: CMP17.P$14 (OUT_13); also elsewhere on the board
FLAG_F6: CMP17.P$15 (OUT_14)
FLAG_I: CMP17.P$1 (OUT_0)
FLAG_N: CMP17.P$2 (OUT_1)
FLAG_V: CMP17.P$4 (OUT_3)
FLAG_X: CMP17.P$5 (OUT_4)
FLAG_Z: CMP17.P$3 (OUT_2)
INSTR_0: CMP15.P$1 (OUT_0); also elsewhere on the board
INSTR_0_N: CMP15.P$9 (OUT_8); also elsewhere on the board
INSTR_1: CMP15.P$2 (OUT_1)
INSTR_1_N: CMP15.P$10 (OUT_9)
INSTR_2: CMP15.P$3 (OUT_2); also elsewhere on the board
INSTR_2_N: CMP15.P$11 (OUT_10); also elsewhere on the board
INSTR_3: CMP15.P$4 (OUT_3); also elsewhere on the board
INSTR_3_N: CMP15.P$12 (OUT_11)
INSTR_4: CMP15.P$5 (OUT_4)
INSTR_4_N: CMP15.P$13 (OUT_12)
INSTR_5: CMP15.P$6 (OUT_5)
INSTR_5_N: CMP15.P$14 (OUT_13)
INSTR_6: CMP15.P$7 (OUT_6)
INSTR_6_N: CMP15.P$15 (OUT_14)
INSTR_7: CMP15.P$8 (OUT_7)
INSTR_7_N: CMP15.P$16 (OUT_15)
MATCH: CMP90.P$1 (OUT_0); also elsewhere on the board
MATCH_N: CMP90.P$2 (OUT_1); also elsewhere on the board
STATE_0: CMP13.P$1 (OUT_0); also elsewhere on the board
STATE_1: CMP13.P$2 (OUT_1); also elsewhere on the board
STATE_2: CMP13.P$3 (OUT_2); also elsewhere on the board
STATE_3: CMP13.P$4 (OUT_3)
STATE_4: CMP13.P$5 (OUT_4)
STATE_5: CMP13.P$6 (OUT_5)
STATE_6: CMP13.P$7 (OUT_6); also elsewhere on the board
STATE_7: CMP13.P$8 (OUT_7); also elsewhere on the board
STATE_8: CMP13.P$9 (OUT_8)
STATE_9: CMP13.P$10 (OUT_9)
STATE_10: CMP13.P$11 (OUT_10)
STATE_11: CMP13.P$12 (OUT_11)
STATE_12: CMP13.P$13 (OUT_12)
STATE_13: CMP13.P$14 (OUT_13)
STATE_14: CMP13.P$15 (OUT_14)
STATE_15: CMP13.P$16 (OUT_15); also elsewhere on the board

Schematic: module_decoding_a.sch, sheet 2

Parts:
CMP2, CMP35: BUS_SPLIT_DISPLAY

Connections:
OPCODE_IS_ABSOLUTE_GROUP: CMP2.P$5 (OUT_4); also elsewhere on the board
OPCODE_IS_ADDQ_GROUP: CMP2.P$11 (OUT_10)
OPCODE_IS_ADDX: CMP35.P$3 (OUT_2)
OPCODE_IS_ADD_GROUP: CMP2.P$12 (OUT_11)
OPCODE_IS_ADD_SP: CMP35.P$10 (OUT_9); also elsewhere on the board
OPCODE_IS_ANDI_PS: CMP35.P$12 (OUT_11); also elsewhere on the board
OPCODE_IS_AND_GROUP: CMP2.P$15 (OUT_14)
OPCODE_IS_BRANCH_GROUP: CMP2.P$3 (OUT_2); also elsewhere on the board
OPCODE_IS_CMP_GROUP: CMP2.P$9 (OUT_8)
OPCODE_IS_DIV: CMP35.P$4 (OUT_3); also elsewhere on the board
OPCODE_IS_DIVS: CMP35.P$5 (OUT_4)
OPCODE_IS_INDIRECT_GROUP: CMP2.P$8 (OUT_7)
OPCODE_IS_INDIRECT_POSTINC: CMP2.P$1 (OUT_0); also elsewhere on the board
OPCODE_IS_JMP_ABS: CMP35.P$13 (OUT_12); also elsewhere on the board
OPCODE_IS_JMP_R0: CMP35.P$14 (OUT_13); also elsewhere on the board
OPCODE_IS_LOGIC_GROUP: CMP2.P$2 (OUT_1)
OPCODE_IS_MOVE_R0_SP: CMP35.P$16 (OUT_15); also elsewhere on the board
OPCODE_IS_MOVE_SP_R0: CMP35.P$15 (OUT_14); also elsewhere on the board
OPCODE_IS_MUL: CMP35.P$7 (OUT_6); also elsewhere on the board
OPCODE_IS_MULS: CMP35.P$8 (OUT_7)
OPCODE_IS_MUL_N: CMP35.P$6 (OUT_5)
OPCODE_IS_NEGX: CMP35.P$1 (OUT_0)
OPCODE_IS_ORI_PS: CMP35.P$11 (OUT_10); also elsewhere on the board
OPCODE_IS_OR_GROUP: CMP2.P$13 (OUT_12)
OPCODE_IS_POSTINC_GROUP: CMP2.P$7 (OUT_6)
OPCODE_IS_SQRT: CMP35.P$9 (OUT_8); also elsewhere on the board
OPCODE_IS_STACK_GROUP: CMP2.P$4 (OUT_3); also elsewhere on the board
OPCODE_IS_STACK_REL_GROUP: CMP2.P$6 (OUT_5); also elsewhere on the board
OPCODE_IS_SUBX: CMP35.P$2 (OUT_1)
OPCODE_IS_SUB_GROUP: CMP2.P$10 (OUT_9)
OPCODE_IS_XOR_GROUP: CMP2.P$14 (OUT_13)

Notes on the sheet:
clBit opcode_is_indirect_postinc; // 0 clBit opcode_is_logic_group; // 1 clBit opcode_is_branch_group; // 2 clBit opcode_is_stack_group; // 3 clBit opcode_is_absolute_group; // 4 clBit opcode_is_stack_rel_group; // 5 clBit opcode_is_postinc_group; // 6 clBit opcode_is_indirect_group; // 7 clBit opc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
clBit opcode_is_negx; // 15 clBit opcode_is_subx; // 14 clBit opcode_is_addx; // 13 clBit opcode_is_div; // 12 clBit opcode_is_divs; // 11 clBit opcode_is_mul_n; // 10 clBit opcode_is_mul; // 9 clBit opcode_is_muls; // 8 clBit opcode_is_sqrt; // 7 clBit opcode_is_add_sp; // 6 clBit opcode_is_ori_ps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

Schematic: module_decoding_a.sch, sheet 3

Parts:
CMP3, CMP47: BUS_SPLIT_DISPLAY

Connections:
BIT_SHIFT_MODE__CHANGE__ARITH: CMP3.P$7 (OUT_6)
BIT_SHIFT_MODE__SET__X_ROT: CMP3.P$8 (OUT_7)
BIT_SHIFT_MODE__TEST_N: CMP3.P$6 (OUT_5)
BIT_SHIFT_MODE___ROT_N: CMP3.P$9 (OUT_8)
DIV_BY_ZERO: CMP47.P$12 (OUT_11); also elsewhere on the board
DIV_BY_ZERO_N: CMP47.P$13 (OUT_12)
OPCODE_IS_ABS: CMP47.P$4 (OUT_3)
OPCODE_IS_BIT_XX: CMP3.P$3 (OUT_2); also elsewhere on the board
OPCODE_IS_BIT_XX_N: CMP3.P$4 (OUT_3)
OPCODE_IS_CMP: CMP47.P$3 (OUT_2)
OPCODE_IS_INV: CMP47.P$8 (OUT_7)
OPCODE_IS_JSR_ABS: CMP3.P$10 (OUT_9); also elsewhere on the board
OPCODE_IS_JSR_R0: CMP3.P$11 (OUT_10); also elsewhere on the board
OPCODE_IS_LDI_X: CMP3.P$1 (OUT_0); also elsewhere on the board
OPCODE_IS_MOVER: CMP47.P$10 (OUT_9)
OPCODE_IS_MUL_SQRT_DIV: CMP47.P$1 (OUT_0); also elsewhere on the board
OPCODE_IS_NEG: CMP47.P$6 (OUT_5)
OPCODE_IS_OR: CMP47.P$7 (OUT_6)
OPCODE_IS_POP_PS: CMP3.P$16 (OUT_15); also elsewhere on the board
OPCODE_IS_POP_RA: CMP47.P$15 (OUT_14); also elsewhere on the board
OPCODE_IS_PUSH_PS: CMP3.P$13 (OUT_12); also elsewhere on the board
OPCODE_IS_PUSH_RA: CMP47.P$16 (OUT_15); also elsewhere on the board
OPCODE_IS_RET: CMP3.P$15 (OUT_14); also elsewhere on the board
OPCODE_IS_RETI: CMP3.P$14 (OUT_13); also elsewhere on the board
OPCODE_IS_SHIFT_BIT: CMP3.P$5 (OUT_4); also elsewhere on the board
OPCODE_IS_SHIFT_XX: CMP3.P$2 (OUT_1); also elsewhere on the board
OPCODE_IS_SUB: CMP47.P$5 (OUT_4)
OPCODE_IS_SXT: CMP47.P$11 (OUT_10)
OPCODE_IS_TEST: CMP47.P$9 (OUT_8)
OPCODE_IS_TRAP: CMP3.P$12 (OUT_11); also elsewhere on the board
OPCODE_IS_X_ARITH: CMP47.P$2 (OUT_1)

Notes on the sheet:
clBit opcode_is_ldi_x; // 0 clBit opcode_is_shift_xx; // 1 clBit opcode_is_bit_xx; // 2 clBit opcode_is_bit_xx_n; // 3 clBit opcode_is_shift_bit; // 4 clBit bit_shift_mode_test_n; // 5 clBit bit_shift_mode_arith; // 6 clBit bit_shift_mode_x_rot; // 7 clBit bit_shift_mode_rot_n; // 8 clBit opcode_is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
clBit opcode_is_mul_sqrt_div; // 0 clBit opcode_is_x_arith; // 1 clBit opcode_is_cmp; // 2 clBit opcode_is_abs; // 3 clBit opcode_is_sub; // 4 clBit opcode_is_neg; // 5 clBit opcode_is_or; // 6 clBit opcode_is_inv; // 7 clBit opcode_is_test; // 8 clBit opcode_is_mover; // 9 clBit opcode_is_sxt; // 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

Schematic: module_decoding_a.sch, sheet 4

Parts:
CMP57: BUS_SPLIT_DISPLAY

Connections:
H_COUNT_IS_15: CMP57.P$3 (OUT_2); also elsewhere on the board
IS_END: CMP57.P$11 (OUT_10); also elsewhere on the board
IS_END_N: CMP57.P$12 (OUT_11)
IS_NOT_INTERRUPTING_END: CMP57.P$14 (OUT_13); also elsewhere on the board
IS_SIMPLE_DATA_TRANSFER: CMP57.P$13 (OUT_12); also elsewhere on the board
LDI_X_STATE_0_BYTE_1_WORD: CMP57.P$9 (OUT_8); also elsewhere on the board
LOAD_WEIGHT: CMP57.P$5 (OUT_4)
OPCODE_IS_JSR_X: CMP57.P$10 (OUT_9); also elsewhere on the board
OPCODE_IS_LD_ST: CMP57.P$8 (OUT_7)
SHIFT_IS_SHIFTING: CMP57.P$4 (OUT_3); also elsewhere on the board
SHIFT_VAL_NON_ZERO: CMP57.P$1 (OUT_0)
SHIFT_VAL_NON_ZERO_N: CMP57.P$2 (OUT_1); also elsewhere on the board
TAKE_INTERRUPT: CMP57.P$7 (OUT_6); also elsewhere on the board
TRAP_STATE_7: CMP57.P$6 (OUT_5); also elsewhere on the board

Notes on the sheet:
clBit shift_val_non_zero; // 0 clBit shift_val_non_zero_n; // 1 clBit h_count_is_15; // 2 clBit shift_is_shifting; // 3 clBit load_weight; // 4 clBit trap_state_7; // 5 clBit take_interrupt; // 6 clBit opcode_is_ld_st; // 7 clBit ldi_x_state_0_byte_1_word; // 8 clBit opcode_is_jsr_x; // 9 clBit is_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

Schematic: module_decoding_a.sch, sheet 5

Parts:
CMP1: DECODER4

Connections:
DIR_SZ_IS_LOAD_BYTE: CMP1.P1; also elsewhere on the board
DIR_SZ_IS_LOAD_WORD: CMP1.P0; also elsewhere on the board
DIR_SZ_IS_STORE_BYTE: CMP1.P3; also elsewhere on the board
DIR_SZ_IS_STORE_WORD: CMP1.P2; also elsewhere on the board
INSTR_2: CMP1.A0; also elsewhere on the board
INSTR_3: CMP1.A1; also elsewhere on the board

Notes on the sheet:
dir_sz_is_load_word = dir_sz_dec.Output()[0]; dir_sz_is_load_byte = dir_sz_dec.Output()[1]; dir_sz_is_store_word = dir_sz_dec.Output()[2]; dir_sz_is_store_byte = dir_sz_dec.Output()[3];

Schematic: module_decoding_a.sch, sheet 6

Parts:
CMP18, CMP19, CMP20, CMP21, CMP41: 2AND

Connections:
OPCODE_IS_ADD_SP: CMP18.P$2 (2); also elsewhere on the board
OPCODE_IS_ADD_SP_STATE_2: CMP18.OUT_P; also elsewhere on the board
OPCODE_IS_BRANCH_GROUP: CMP19.P$2 (2); also elsewhere on the board
OPCODE_IS_BXX_STATE_2: CMP19.OUT_P; also elsewhere on the board
OPCODE_IS_DIV: CMP41.P$2 (2); also elsewhere on the board
OPCODE_IS_DIV_STATE_0: CMP41.OUT_P; also elsewhere on the board
OPCODE_IS_JSR_X: CMP21.P$1 (1); also elsewhere on the board
OPCODE_IS_JSR_X_STATE_7: CMP21.OUT_P; also elsewhere on the board
OPCODE_IS_STACK_REL_GROUP: CMP20.P$2 (2); also elsewhere on the board
OPCODE_IS_STACK_REL_STATE_2: CMP20.OUT_P; also elsewhere on the board
STATE_0: CMP41.P$1 (1); also elsewhere on the board
STATE_2: CMP18.P$1 (1), CMP19.P$1 (1), CMP20.P$1 (1); also elsewhere on the board
STATE_7: CMP21.P$2 (2); also elsewhere on the board

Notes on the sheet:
opcode_is_div_state_0 = Cpnt_2AND(opcode_is_div, bus_state[0]);
opcode_is_bxx_state_2 = Cpnt_2AND(opcode_is_branch_group, bus_state[2]);
opcode_is_add_sp_state_2 = Cpnt_2AND(opcode_is_add_sp, bus_state[2]);
opcode_is_stack_rel_state_2 = Cpnt_2AND(opcode_is_stack_rel_group, bus_state[2]);
opcode_is_jsr_x_state_7 = Cpnt_2AND(opcode_is_jsr_x, bus_state[7]);

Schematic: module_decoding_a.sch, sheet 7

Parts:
CMP31: 4X2AND_OR
CMP32, CMP34: 2X2AND_OR
CMP33: 2OR
CMP65, CMP66: 2AND

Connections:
DIR_SZ_IS_STORE_BYTE: CMP34.P$2 (A1); also elsewhere on the board
DIR_SZ_IS_STORE_WORD: CMP32.P$4 (B1); also elsewhere on the board
H_COUNT_IS_15: CMP65.P$2 (2); also elsewhere on the board
INSTR_0_N: CMP65.P$1 (1); also elsewhere on the board
INSTR_2_N: CMP66.P$2 (2); also elsewhere on the board
IS_SIMPLE_DATA_TRANSFER: CMP31.P$7 (D0); also elsewhere on the board
unnamed: CMP31.P$1 (A0), CMP31.P$2 (A1)
OPCODE_IS_ABSOLUTE_GROUP: CMP31.P$6 (C1); also elsewhere on the board
OPCODE_IS_JSR_R0: CMP32.P$2 (A1); also elsewhere on the board
OPCODE_IS_LDI_X: CMP66.P$1 (1); also elsewhere on the board
OPCODE_IS_STACK_REL_STATE_2: CMP31.P$3 (B0), CMP31.P$4 (B1); also elsewhere on the board
START_TRANSFER_CYCLE: CMP31.OUT_P, CMP32.P$3 (B0), CMP34.P$1 (A0); also elsewhere on the board
STATE_0: CMP31.P$8 (D1), CMP32.P$1 (A0); also elsewhere on the board
STATE_1: CMP31.P$5 (C0); also elsewhere on the board
STATE_6: CMP34.P$3 (B0), CMP34.P$4 (B1); also elsewhere on the board
STATE_15: CMP33.P$1 (A2); also elsewhere on the board
UNSIGNED_15: CMP65.OUT_P; also elsewhere on the board
WILL_BE_1__LDI: CMP66.OUT_P; also elsewhere on the board
WILL_BE_6__SET_A: CMP32.OUT_P, CMP33.P$2 (A1)
WILL_BE_STATE_6: CMP33.OUT_P; also elsewhere on the board
WILL_BE_STATE_7: CMP34.OUT_P; also elsewhere on the board

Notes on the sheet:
unsigned_15 = Cpnt_2AND(h_count_is_15, type_bit_is_unsigned);
start_transfer_cycle = Cpnt_4x2AND_OR( bus_state[0], is_simple_data_transfer, bus_state[1], opcode_is_absolute_group, opcode_is_stack_rel_state_2, opcode_is_stack_rel_state_2, // MOPUP BIT_VAL_0, BIT_VAL_0);
will_be_1__ldi = Cpnt_2AND(opcode_is_ldi_x, ~size_bit_is_byte);
will_be_6__set_A = Cpnt_2x2AND_OR(dir_sz_is_store_word, start_transfer_cycle, bus_state[0], opcode_is_jsr_r0);
will_be_6 = Cpnt_2OR( will_be_6__set_A, bus_state[15]);
will_be_7 = Cpnt_2x2AND_OR(bus_state[6],bus_state[6], // MOPUP dir_sz_is_store_byte, start_transfer_cycle);

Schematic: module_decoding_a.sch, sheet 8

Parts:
CMP25, CMP26, CMP73, CMP92: 2OR
CMP86, CMP88: 2AND

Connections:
BRANCH_NOT_TAKEN: CMP88.OUT_P; also elsewhere on the board
BRANCH_TAKEN: CMP86.OUT_P; also elsewhere on the board
MATCH: CMP86.P$2 (2); also elsewhere on the board
MATCH_N: CMP88.P$2 (2); also elsewhere on the board
OPCODE_IS_ANDI_ORI_PS: CMP25.OUT_P; also elsewhere on the board
OPCODE_IS_ANDI_PS: CMP25.P$2 (A1); also elsewhere on the board
OPCODE_IS_BRANCH_GROUP: CMP88.P$1 (1); also elsewhere on the board
OPCODE_IS_MOVER_SP: CMP26.OUT_P; also elsewhere on the board
OPCODE_IS_MOVE_R0_SP: CMP26.P$1 (A2); also elsewhere on the board
OPCODE_IS_MOVE_SP_R0: CMP26.P$2 (A1); also elsewhere on the board
OPCODE_IS_ORI_PS: CMP25.P$1 (A2); also elsewhere on the board
OPCODE_IS_POP_PS: CMP92.P$1 (A2); also elsewhere on the board
OPCODE_IS_POP_RA: CMP92.P$2 (A1); also elsewhere on the board
OPCODE_IS_POP_RA_PS: CMP92.OUT_P; also elsewhere on the board
OPCODE_IS_RET: CMP73.P$1 (A2); also elsewhere on the board
OPCODE_IS_RETI: CMP73.P$2 (A1); also elsewhere on the board
OPCODE_IS_RET_RETI: CMP73.OUT_P; also elsewhere on the board
STATE_0: CMP86.P$1 (1); also elsewhere on the board

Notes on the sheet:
opcode_is_andi_ori_ps = Cpnt_2OR(opcode_is_andi_ps, opcode_is_ori_ps);
opcode_is_mover_sp = Cpnt_2OR(opcode_is_move_sp_r0, opcode_is_move_r0_sp);
opcode_is_ret_reti = Cpnt_2OR(opcode_is_ret, opcode_is_reti);
opcode_is_pop_ra_ps = Cpnt_2OR(opcode_is_pop_ra, opcode_is_pop_ps);
branch_taken = Cpnt_2AND(bus_state[0], bus_match_cc.match);
branch_not_taken = Cpnt_2AND(opcode_is_branch_group, bus_match_cc.match_n);
